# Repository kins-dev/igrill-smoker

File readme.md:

# Starting with Raspberry Pi Stretch 

<!-- markdownlint-disable MD036 -->
**&#x1F534; Note: You are 100% responsible for ensuring safe food practices are followed**

**&#x1F534; Check and modify temperatures as appropriate**
<!-- markdownlint-enable MD036 -->

<!-- markdownlint-disable MD033 -->
<h2>Table of Contents</h2>
<!-- markdownlint-enable MD033 -->
<!-- markdownlint-disable MD039 -->
<!-- @import "[TOC]" {cmd="toc" depthFrom=2 depthTo=6 orderedList=false} -->

<!-- code_chunk_output -->

- [Problem Statement](#problem-statement)
- [Versions](#versions)
- [Design](#design)
- [Equipment](#equipment)
- [Requirements](#requirements)
- [Installation](#installation)
- [Software Setup](#software-setup)
- [Using iGrill Mini](#using-igrill-mini)
- [Grill Setup](#grill-setup)
- [Running](#running)
- [Lighttpd Setup](#lighttpd-setup)
- [Project Notes](#project-notes)
- [iGrill Smoker Board Rev. *A](#igrill-smoker-board-rev-a)
  - [*A Board](#a-board)
  - [*A Notes](#a-notes)
  - [*A Parts](#a-parts)
- [iGrill Smoker Board Rev. *B](#igrill-smoker-board-rev-b)
  - [*B Board](#b-board)
  - [*B Notes](#b-notes)
  - [*B Parts](#b-parts)
- [iGrill Smoker Board Rev. *C](#igrill-smoker-board-rev-c)
  - [*C Board](#c-board)
  - [*C Notes](#c-notes)
  - [*C Parts](#c-parts)
- [iGrill Smoker Board Rev. *D](#igrill-smoker-board-rev-d)
  - [*D Notes](#d-notes)
  - [*D Parts](#d-parts)
- [iGrill Smoker Board Rev. *E](#igrill-smoker-board-rev-e)
  - [*E Notes](#e-notes)
  - [*E Parts](#e-parts)

<!-- /code_chunk_output -->

<!-- markdownlint-enable MD039 -->
## Problem Statement

Create a low cost smoking unit that can be controlled/monitored via the internet.

## Versions

- v1.0: Whole System
- v1.1: BLE Improvements
- v1.2: Python3 Support
- v1.3: Temperature Range Support
- v1.4: SSR Support
- v1.5: PID control

## Design

See the [design document](documentation/iGrill_smoker_design.md).

## Equipment

Prices as of June 10th, 2019.  Some items like the hotplates or skillet can be found at Goodwill instead.  Total cost (new) $287.96.  Every item can be used for more than one task.  Meat, wood chips, and extension cords not included.

- [Weber Grill](https://www.amazon.com/Weber-741001-Original-22-Inch-Charcoal/dp/B00004RALU/ref=sr_1_3) - $109
- [iGrill2](https://www.amazon.com/Weber-7203-iGrill-2-Thermometer/dp/B01MG2CNDL/ref=sr_1_3) - $64.99
- [Hotplate](https://www.amazon.com/Cuisine-ESB-300X-Maxi-Matic-Single-Electric/dp/B0006A2ZTS/ref=sr_1_70) - 2x @ $12.96
- [TP-Link Kasa](https://www.amazon.com/TP-Link-HS100-Required-Google-Assistant/dp/B0178IC734/ref=sr_1_4) - $14.69
- [Raspberry Pi](https://www.target.com/p/raspberry-pi-3-model-b-project-board/-/A-53349740) - $34.49
- [SD Card](https://www.amazon.com/Kingston-Digital-microSDHC-SDC4-8GBSP/dp/B0027CA7UW/ref=sr_1_11) - $3.99
- [Skillets](https://www.amazon.com/dp/B073Q8P6C8/ref=psdc_289821_t1_B00008GKDN) - 2x @ $10.93
- [8 inch rings](https://www.amazon.com/Ateco-14408-8-Inch-Stainless-Cutter/dp/B002A5BU5M/ref=pd_sbs_79_5/140-6446357-6003018) - 2x @ $6.51

## Requirements

You must have:

- Raspberry Pi 3
- TP-Link Kasa
- iGrill2 or iGrill3 (iGrill mini coming soon for time based smoking)

Optional items:

- LEDs with current limiting resistors
- Speaker with 3.5 mm stereo jack input

*Note: This has been tested using a Raspberry Pi B 3 with Raspian Stretch.  Your milage may vary.*

This guide assumes you've done the basic setup of network and updated the system on your Raspberry Pi.  Remember, you probably want to enable ssh access.  You must have your iGrill ready to complete the installation and setup.  This does require python 3 to be installed.

## Installation

Either download and run ```auto-install.sh``` from the installation directory or run the following commands:

```bash
git clone https://git.kins.dev/igrill-smoker
cd igrill-smoker/install
bash run-install.sh
```

After starting the ```run-install.sh``` script, you should turn on your iGrill v2.  Installation shouldn't take long and the device is needed for setup.

## Software Setup

Copy ```config/iGrill_config.example.ini``` to ```config/iGrill_config.ini```.  Update ```iGrill_config.ini``` with any system settings you want to change.

Here is what that file looks like:
<!-- TODO: add > at the end of this line, open MPE, and use shift enter to regenerate --
```bash {cmd hide modify_source}
echo -n \`\`\`ini
cat config/iGrill_config.example.ini
echo -n \`\`\`
```
<!---->

<!-- code_chunk_output -->

```ini
# Copyright (c) 2019:   Scott Atkins <scott@kins.dev>
#                       (https://git.kins.dev/igrill-smoker)
# License:              MIT License
#                       See the LICENSE file
[iGrill]
# can be Standard or Mini
Type=Standard

[Probes]
# For iGrill mini set food probe to 0 and smoke probe to 1

# Food probe must be set between 0 and 4, where 0 means the
# probe is disabled.  The left most probe is 1 and right most
# is 4 on the iGrill 2/3
#
# If you disable the food probe, you must use a stage that
# is iGrill mini compatible (see stage file) or disable stages
FoodProbe=1

# Smoke probe must be set between 1 and 4.  The left most probe
# is 1 and right most is 4 on the iGrill 2/3
SmokeProbe=4

[RuntimeFiles]
# Where the limits file should exist, relative to the project
# directory
LimitsFile=limits.ini
TempDataFile=igrill.json

[Logging]
LogLevel=INFO
LogFile=

[Kasa]
# Name of your plug in the Kasa app, case sensitive
Name=iGrill-smoker

[Smoking]
MaxTempChange=2
TempBandSize=7

# Can be the name of any file in the stages directory (excluding the .sh) or None
Food=brisket

# Only valid if Food=None
SmokeMid=225
InternalTarget=185

# Used to specify the solid state relay board
[SSR]
# Possible values:
#  **, *A, *B, *C, *D, *D.1, *E, Auto, None
Board=Auto

[Reporting]
# time in seconds between polls of the iGrill
# faster polling means more power use
PollTime=20

ResultsDirectory=/var/www/html
CSVFile=current.csv
StateFile=state.json
```

<!-- /code_chunk_output -->

Edit the chart.html file in the website_example directory to suit your needs and copy it to your ```/var/www/html``` directory.

## Using iGrill Mini

The iGrill mini has a single probe.  That means you can either monitor the smoke temperature or the food temperature.  Since this is controlling a plug for the smoke, you should not monitor the food temperature via the iGrill mini probe.  Follow the instructions in iGrill_config.example.ini for setting the probe values.

## Grill Setup

## Running

Start a smoking session by running:

```bash
./start_smoking.sh
```

## Lighttpd Setup

Secure your instance of lighttpd using the instructions at <https://github.com/galeone/letsencrypt-lighttpd/blob/master/renew.sh>.  You may want a wildcard certificate and you can find instructions via <https://asknetsec.com/generate-lets-encrypt-free-wildcard-certificate-using-certbot-ubuntu-16-04/>.  Check your SSL setup via <https://www.ssllabs.com/ssltest/index.html>.

Also, it may be a good idea to setup lighttpd such that ```*.csv```/```*.json``` is not cached.  Here's an example lighttpd config file:

```ruby
server.modules = (
        "mod_expire",
        "mod_access",
        "mod_alias",
        "mod_compress",
        "mod_redirect",
        "mod_setenv",
        "mod_dirlisting",
)

server.document-root                            = "/var/www/html"
server.upload-dirs                              = ( "/var/cache/lighttpd/uploads" )
server.errorlog                                 = "/var/log/lighttpd/error.log"
server.pid-file                                 = "/var/run/lighttpd.pid"
server.username                                 = "www-data"
server.groupname                                = "www-data"
server.port                                     = 80

index-file.names                                = ( "index.php", "index.html", "index.lighttpd.html" )
url.access-deny                                 = ( "~", ".inc" )
static-file.exclude-extensions                  = ( ".php", ".pl", ".fcgi" )

compress.cache-dir                              = "/var/cache/lighttpd/compress/"
compress.filetype                               = ( "application/javascript", "text/css", "text/html", "text/plain" )

# default listening port for IPv6 falls back to the IPv4 port
## Use ipv6 if available
#include_shell "/usr/share/lighttpd/use-ipv6.pl " + server.port
include_shell "/usr/share/lighttpd/create-mime.assign.pl"
include_shell "/usr/share/lighttpd/include-conf-enabled.pl"

# SSL Config
$SERVER["socket"] == ":443" {
        protocol                                = "https://"
        ssl.engine                              = "enable"
        ssl.ca-file                             = "/etc/lighttpd/fullchain.pem"
        ssl.pemfile                             = "/etc/lighttpd/wildcard.cert.pem"

        setenv.add-environment  = (
                "HTTPS"                         => "on"
        )

        setenv.add-response-header  = (
                # Allow cross domain access
                # Safari requires *
                "Access-Control-Allow-Origin"   => "*",

                # Used to identify the server based on headers
                "Server"                        => "Server name",

                # Set timeout for ssl access
                "Strict-Transport-Security"     => "max-age=15768000;"
        )

        # Mitigate BEAST attack:
        #
        # A stricter base cipher suite. For details see:
        # http://blog.ivanristic.com/2011/10/mitigating-the-beast-attack-on-tls.html
        ssl.cipher-list                         = "ECDHE-ECDSA-AES256-GCM-SHA384:ECDHE-RSA-AES256-GCM-SHA384:ECDHE-ECDSA-CHACHA20-POLY1305:ECDHE-RSA-CHACHA20-POLY1305:ECDHE-ECDSA-AES128-GCM-SHA256:ECDHE-RSA-AES128-GCM-SHA256:ECDHE-ECDSA-AES256-SHA384:ECDHE-RSA-AES256-SHA384:ECDHE-ECDSA-AES128-SHA256:ECDHE-RSA-AES128-SHA256"

        # Make the server prefer the order of the server side cipher suite instead of the client suite.
        # This is necessary to mitigate the BEAST attack (unless you disable all non RC4 algorithms).
        # This option is enabled by default, but only used if ssl.cipher-list is set.
        ssl.honor-cipher-order                  = "enable"

        # Mitigate CVE-2009-3555 by disabling client triggered renegotiation
        # This is enabled by default.
        ssl.disable-client-renegotiation        = "enable"
        ssl.ec-curve                            = "secp384r1"
        ssl.use-compression                     = "disable"

        # Disable SSLv2 because is insecure
        ssl.use-sslv2                           = "disable"

        # Disable SSLv3 (can break compatibility with some old browser) /cares
        ssl.use-sslv3                           = "disable"
}

# Prevent caching of json/csv files
$HTTP["url"] =~ "/.*\.(json|csv)$" {
        expire.url = (
                ""                              => "access 0 seconds",
        )
}
```

## Project Notes

1.3 Uses TP-Link Kasa for power control.  1.4 includes a brand new power control board that plugs into the Raspberry Pi which will allow much more fine grain control of the smoker temperature.

This is necessary because the relay in the TP-Link won't handle the number of on/off cycles required.  Instead a solid state relay is used.  A word of caution, this is not UL rated or certified.  If you don't know which end of the soldering iron to hold, then you probably should just stick with 1.3.

The TP-Link Kasa plug will still be used as a failsafe device in the system.

## iGrill Smoker Board Rev. *A

### *A Board

This board has a buzzer, two LEDs and connection points for the solid state relay.  It sits off the edge of the Raspberry Pi GPIOs.

### *A Notes

This board should not be used.

Features

- Two LEDs
- Buzzer
- Small design

Defects

- The spacing for the resistors is off
- Hard to hand solder
- Hangs off the board the wrong way
- Red LED stays on due to leakage current
- Leakage current to the SSR

### *A Parts

- Header (2x20): [DigiKey](https://www.digikey.com/product-detail/en/sullins-connector-solutions/SFH11-PBPC-D20-ST-BK/S9200-ND/1990093) $1.94
- LED (Green): [DigiKey](https://www.digikey.com/product-detail/en/lite-on-inc/LTL-4233/160-1130-ND/217580) $0.36
- LED (Red): [DigiKey](https://www.digikey.com/product-detail/en/wurth-electronics-inc/151051RS11000/732-5016-ND/4490012) $0.15
- Resistors (100 ohm x2): [DigiKey](https://www.digikey.com/product-detail/en/stackpole-electronics-inc/CF14JT100R/CF14JT100RCT-ND/1830327) $0.10
- Buzzer: [DigiKey](https://www.digikey.com/product-detail/en/tdk-corporation/PS1240P02BT/445-2525-1-ND/935930) $0.68

## iGrill Smoker Board Rev. *B

### *B Board

This board has a buzzer, two LEDs and connection points for the solid state relay.  It sits on the Raspberry Pi GPIOs.

### *B Notes

This board should not be used.

New Features

- Sits over the Pi with mounting holes
- Board auto detect works
- Buzzer switch

Defects

- The spacing for the resistors is off
- The QR code doesn't always read correctly
- The solder mask makes it hard to read the @ symbol
- Red LED stays on due to leakage current
- Buzzer makes a sound when it shouldn't
- Leakage current to the SSR

### *B Parts

- Header (2x20): [DigiKey](https://www.digikey.com/product-detail/en/sullins-connector-solutions/SFH11-PBPC-D20-ST-BK/S9200-ND/1990093) $1.94
- LED (Green): [DigiKey](https://www.digikey.com/product-detail/en/lite-on-inc/LTL-4233/160-1130-ND/217580) $0.36
- LED (Red): [DigiKey](https://www.digikey.com/product-detail/en/wurth-electronics-inc/151051RS11000/732-5016-ND/4490012) $0.15
- Resistors (100 ohm x2): [DigiKey](https://www.digikey.com/product-detail/en/stackpole-electronics-inc/CF14JT100R/CF14JT100RCT-ND/1830327) $0.10
- Buzzer: [DigiKey](https://www.digikey.com/product-detail/en/tdk-corporation/PS1240P02BT/445-2525-1-ND/935930) $0.68
- Switch: [DigiKey](https://www.digikey.com/product-detail/en/c-k-components/JS202011CQN/401-2001-ND/1640097) $0.43

## iGrill Smoker Board Rev. *C

### *C Board

This board has a buzzer, two LEDs and a terminal block for the solid state relay.  It sits on the Raspberry Pi GPIOs.

### *C Notes

This board is currently in production and has not been tested.

New Features

- NPN transistors to remove leakage

Fixes

- QR Code
- Resistor spacing
- Solder mask changed to silk screen for fine pitch
- Using suggested design for the buzzer

Defects

- Leakage current to the SSR
- Missing resistors on NPN transistor base (good design practice)

### *C Parts

- Header (2x20): [DigiKey](https://www.digikey.com/product-detail/en/sullins-connector-solutions/SFH11-PBPC-D20-ST-BK/S9200-ND/1990093) $1.94
- LED (Green): [DigiKey](https://www.digikey.com/product-detail/en/lite-on-inc/LTL-4233/160-1130-ND/217580) $0.36
- LED (Red): [DigiKey](https://www.digikey.com/product-detail/en/wurth-electronics-inc/151051RS11000/732-5016-ND/4490012) $0.15
- Resistors (100 ohm x3): [DigiKey](https://www.digikey.com/product-detail/en/stackpole-electronics-inc/CF14JT100R/CF14JT100RCT-ND/1830327) $0.10
- Buzzer: [DigiKey](https://www.digikey.com/product-detail/en/tdk-corporation/PS1240P02BT/445-2525-1-ND/935930) $0.68
- Switch: [DigiKey](https://www.digikey.com/product-detail/en/c-k-components/JS202011CQN/401-2001-ND/1640097) $0.43
- Transistors (NPN x3): [DigiKey](https://www.digikey.com/product-detail/en/micro-commercial-co/2N3904-AP/2N3904-APCT-ND/950591) $0.19

## iGrill Smoker Board Rev. *D

This board has a buzzer, seven LEDs and connection points for the solid state relay.  It sits on the Raspberry Pi GPIOs.

### *D Notes

The boards back from production are bad

New Features

- Five new LEDs for temperature monitoring
- Surface mount parts
- Mosfet transistors so a resistor is no longer needed
- Transistor to prevent SSR leakage
- Cheaper parts

Defects

- Silk screen issue
- QR Code issue (too small, inverted on back)
- Transistors wired backwards

### *D Parts

TODO: Add part list

## iGrill Smoker Board Rev. *E

This board has a buzzer, seven LEDs and connection points for the solid state relay.  It sits on the Raspberry Pi GPIOs.  It also has jumpers for a board id number

### *E Notes

This board is not yet in production and has not been tested.

New Features

- New QR code
- Pull down resistors for all transistors

Defects

- None found yet

### *E Parts

TODO: Add part list

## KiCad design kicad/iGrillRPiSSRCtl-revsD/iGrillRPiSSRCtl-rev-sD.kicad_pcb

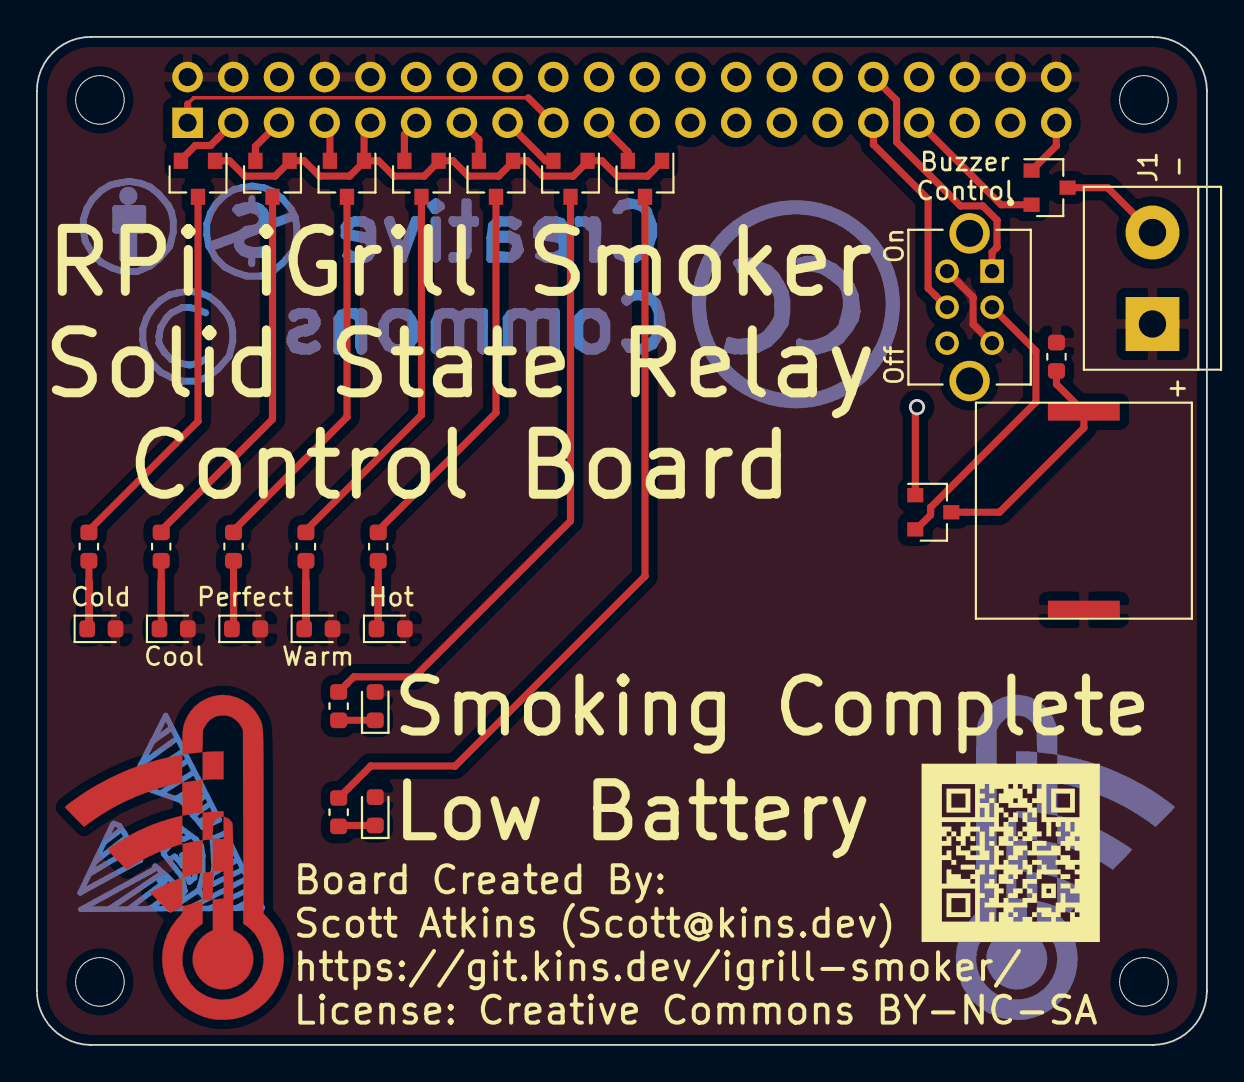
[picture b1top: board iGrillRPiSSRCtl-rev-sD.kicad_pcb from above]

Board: 2 copper layers, 65.0 x 56.0 mm, 32 parts (1 on the bottom side), 30 nets.

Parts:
BZ1: Buzzer; Buzzer_KELIKING_KLJ-1230-smd
D1: Low Battery; LED_0603_1608Metric
D2: Smoking Complete; LED_0603_1608Metric
D3: Hot; LED_0603_1608Metric
D4: Warm; LED_0603_1608Metric
D5: Perfect; LED_0603_1608Metric
D6: Cool; LED_0603_1608Metric
D7: Cold; LED_0603_1608Metric
J1: Screw_Terminal_01x02; TerminalBlock_bornier-2_P5.08mm
MK1, MK2, MK3, MK4: M2.5; MountingHole_2.7mm_M2.5
P1: Conn_02x20_Odd_Even; PinSocket_2x20_P2.54mm_Vertical
Q1, Q2, Q3, Q4, Q5, Q6, Q7, Q8, Q9: Q_NPN_ECB; SOT-23
R1, R5, R6, R8, R9: 120Ω; R_0603_1608Metric
R2, R7: 82Ω; R_0603_1608Metric
R4: 1kΩ; R_0603_1608Metric
SW1: Off On; SW_OS202011MS2QS1

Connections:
+3V3: P1.1, P1.17
+5V: BZ1.1, D1.2, D2.2, D3.2, D4.2, D5.2, D6.2, D7.2, J1.1, P1.2, P1.4, P1.8, P1.10, P1.36, P1.38, P1.40, R4.1, SW1.3, SW1.4
/GPIO2(SDA1): P1.3, Q8.2
/GPIO3(SCL1): P1.5, Q7.2
/GPIO4(GCLK): P1.7, Q6.2
/GPIO6: P1.31, SW1.5
/GPIO10(SPI0_MOSI): P1.19, Q2.2
/GPIO12(PWM0): P1.32, SW1.1
/GPIO13(PWM1): P1.33, Q9.2
/GPIO17(GEN0): P1.11, Q5.2
/GPIO22(GEN3): P1.15, Q3.2
/GPIO27(GEN2): P1.13, Q4.2
GND: P1.6, P1.9, P1.12, P1.14, P1.16, P1.18, P1.20, P1.22, P1.24, P1.25, P1.26, P1.30, P1.34, P1.39, Q1.1, Q2.1, Q3.1, Q4.1, Q5.1, Q6.1, Q7.1, Q8.1, Q9.1, SW1.6
unnamed: BZ1.2, Q1.3, R4.2
unnamed: D1.1, R1.1
unnamed: D2.1, R2.1
unnamed: D3.1, R5.1
unnamed: D4.1, R6.1
unnamed: D5.1, R7.1
unnamed: D6.1, R8.1
unnamed: D7.1, R9.1
unnamed: J1.2, Q9.3
unnamed: Q1.2, SW1.2
unnamed: Q2.3, R1.2
unnamed: Q3.3, R2.2
unnamed: Q4.3, R5.2
unnamed: Q5.3, R6.2
unnamed: Q6.3, R7.2
unnamed: Q7.3, R8.2
unnamed: Q8.3, R9.2

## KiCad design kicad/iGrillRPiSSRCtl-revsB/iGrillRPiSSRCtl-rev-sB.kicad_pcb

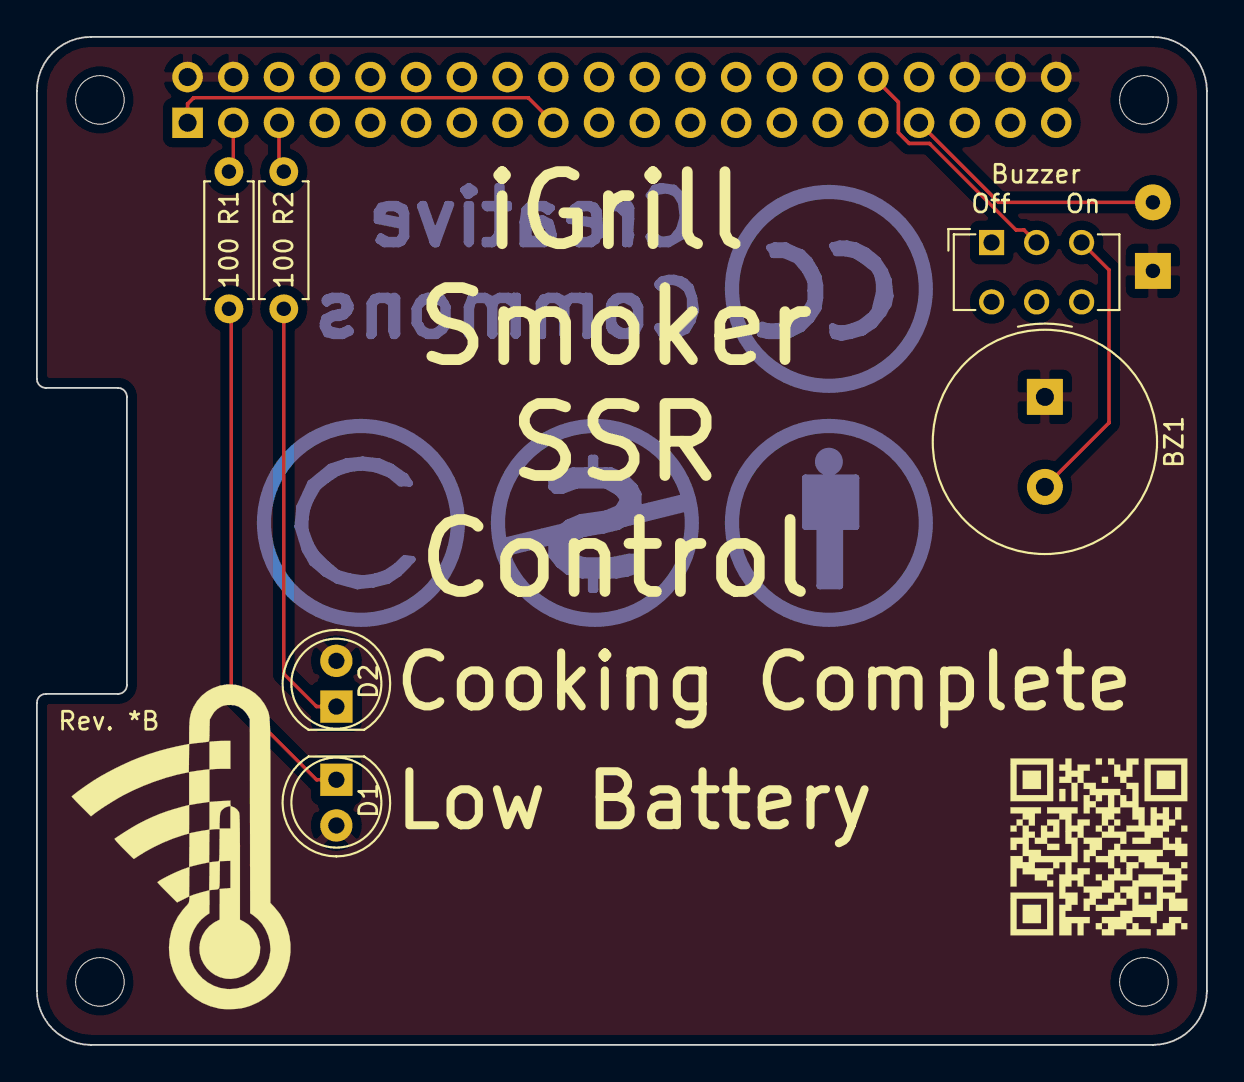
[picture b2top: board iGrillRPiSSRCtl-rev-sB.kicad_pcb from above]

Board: 2 copper layers, 65.0 x 56.0 mm, 12 parts (1 on the bottom side), 10 nets.

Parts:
BZ1: Buzzer; Buzzer_TDK_PS1240P02BT_D12.2mm_H6.5mm
D1: Low Battery; LED_D5.0mm
D2: Cooking Complete; LED_D5.0mm_Clear
J1: Conn_01x02; SolderWirePad_1x02_P3.81mm_Drill0.8mm
MK1, MK2, MK3, MK4: M2.5; MountingHole_2.7mm_M2.5
Off    On: SW_DPDT_x2; SW_CuK_JS202011CQN_DPDT_Straight
P1: Conn_02x20_Odd_Even; PinSocket_2x20_P2.54mm_Vertical
R1, R2: 100; R_Axial_DIN0207_L6.3mm_D2.5mm_P7.62mm_Horizontal

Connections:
+3V3: P1.1, P1.17
+5V: BZ1.1, D1.2, D2.2, J1.1, P1.2, P1.4, P1.8, P1.36, P1.38, P1.40
/GPIO2(SDA1): P1.3, R1.1
/GPIO3(SCL1): P1.5, R2.1
/GPIO12(PWM0): Off On.2, P1.32
/GPIO13(PWM1): J1.2, P1.33
GND: P1.6, P1.9, P1.10, P1.12, P1.14, P1.16, P1.18, P1.20, P1.22, P1.24, P1.25, P1.26, P1.30, P1.34, P1.39
unnamed: BZ1.2, Off On.3
unnamed: D1.1, R1.2
unnamed: D2.1, R2.2

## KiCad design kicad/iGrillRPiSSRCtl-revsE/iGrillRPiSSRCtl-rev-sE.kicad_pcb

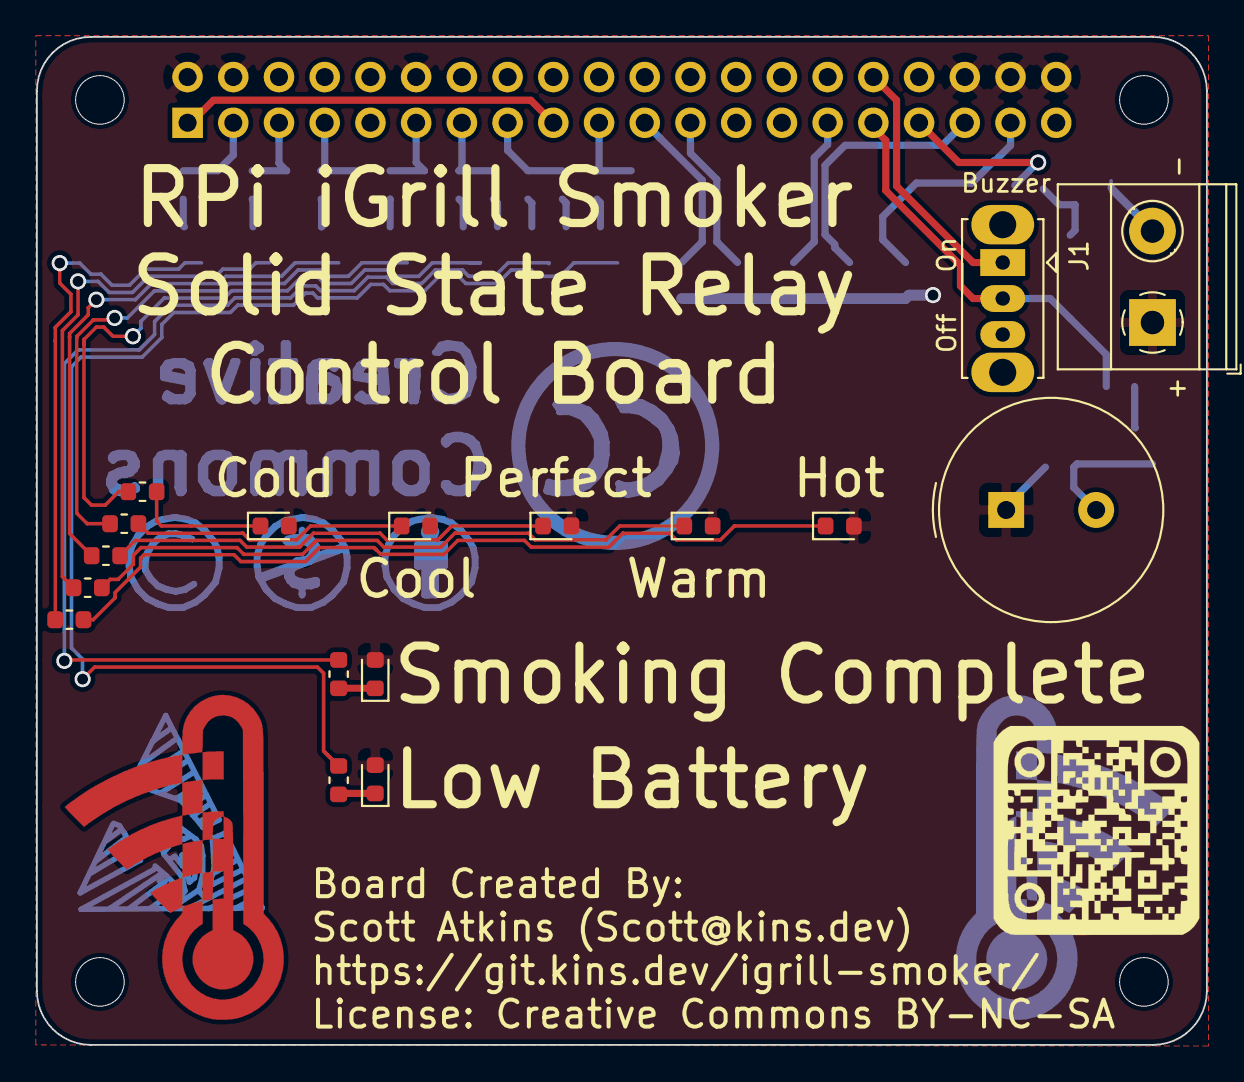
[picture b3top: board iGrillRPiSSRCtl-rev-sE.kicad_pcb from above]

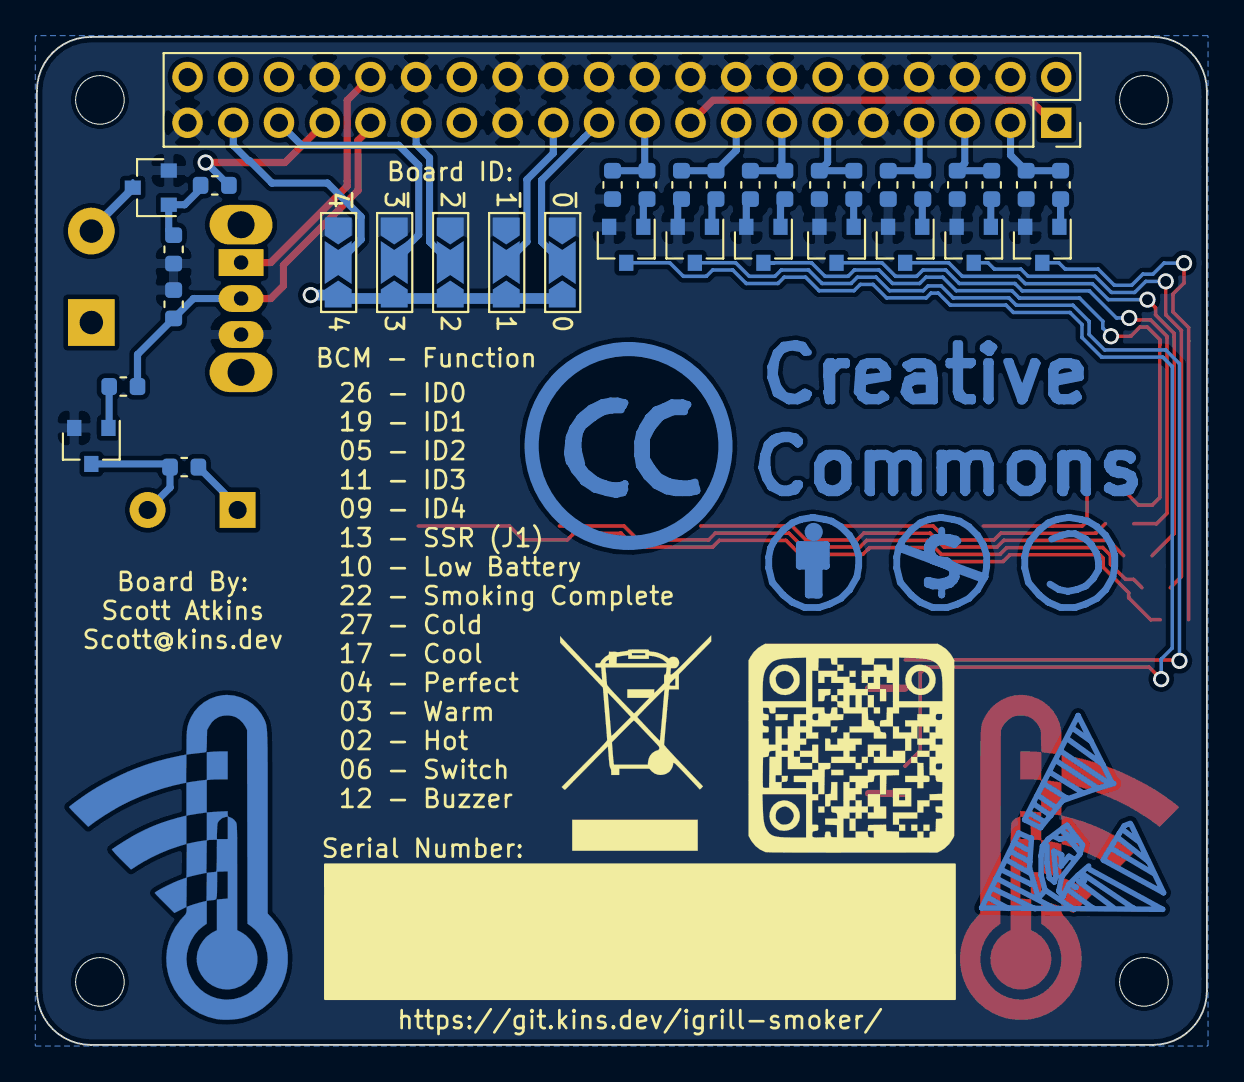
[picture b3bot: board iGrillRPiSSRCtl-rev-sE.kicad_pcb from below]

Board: 2 copper layers, 65.0 x 56.0 mm, 55 parts (34 on the bottom side), 43 nets.

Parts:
BZ1: Buzzer; Buzzer_TDK_PS1240P02BT_D12.2mm_H6.5mm
D1: Low Battery; LED_0603_1608Metric
D2: Smoking Complete; LED_0603_1608Metric
D3: Cold; LED_0603_1608Metric
D4: Cool; LED_0603_1608Metric
D5: Perfect; LED_0603_1608Metric
D6: Warm; LED_0603_1608Metric
D7: Hot; LED_0603_1608Metric
J1: Screw_Terminal_01x02; TerminalBlock_Phoenix_MKDS-1,5-2-5.08_1x02_P5.08mm_Horizont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
JP1, JP2, JP3, JP4, JP5: Jumper_3_Open; SolderJumper-3_P2.0mm_Open_TrianglePad1.0x1.5mm_NumberLabels
MK1, MK2, MK3, MK4: M2.5; MountingHole_2.7mm_M2.5
P1: Conn_02x20_Odd_Even; PinSocket_2x20_P2.54mm_Vertical
Q1, Q2, Q3, Q4, Q5, Q6, Q7, Q8, Q9: MMBT3904LT1G; SOT-23
R1, R3, R5, R7, R9, R12, R14: 180Ω; R_0603_1608Metric
R2, R4, R6, R8, R10, R11, R13, R15, R16, R17: 1kΩ; R_0603_1608Metric
R18, R19, R20, R21, R22, R23, R24, R25, R26: 10kΩ; R_0603_1608Metric
SW1: SW_SPDT; SW_Slide_1P2T_CK_OS102011MS2Q

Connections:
+3V3: P1.1, P1.17
+5V: BZ1.1, D1.2, D2.2, D3.2, D4.2, D5.2, D6.2, D7.2, J1.1, JP1.3, JP2.3, JP3.3, JP4.3, JP5.3, P1.2, P1.4, P1.12, P1.36, P1.38, P1.40, R17.1
/GPIO2(SDA1): P1.3, R15.2, R25.1
/GPIO3(SCL1): P1.5, R13.2, R24.1
/GPIO4(GCLK): P1.7, R10.2, R23.1
/GPIO5: JP3.2, P1.29
/GPIO6: P1.31, R16.1, R26.2, SW1.2
/GPIO9(SPI0_MISO): JP1.2, P1.21
/GPIO10(SPI0_MOSI): P1.19, R2.2, R18.1
/GPIO11(SPI0_SCK): JP2.2, P1.23
/GPIO12(PWM0): P1.32, SW1.1
/GPIO13(PWM1): P1.33, R11.1
/GPIO17(GEN0): P1.11, R8.2, R21.1
/GPIO19(SPI1_MISO): JP4.2, P1.35
/GPIO22(GEN3): P1.15, R4.2, R19.1
/GPIO26: JP5.2, P1.37
/GPIO27(GEN2): P1.13, R6.2, R20.1
GND: JP1.1, JP2.1, JP3.1, JP4.1, JP5.1, P1.6, P1.8, P1.9, P1.10, P1.14, P1.16, P1.18, P1.20, P1.22, P1.24, P1.25, P1.26, P1.30, P1.34, P1.39, Q1.2, Q2.2, Q3.2, Q4.2, Q5.2, Q6.2, Q7.2, Q8.2, Q9.2, R18.2, R19.2, R20.2, R21.2, R22.1, R23.2, R24.2, R25.2, R26.1, SW1.3
unnamed: BZ1.2, Q9.3, R17.2
unnamed: D1.1, R1.1
unnamed: D2.1, R3.1
unnamed: D3.1, R5.1
unnamed: D4.1, R7.1
unnamed: D5.1, R9.1
unnamed: D6.1, R12.1
unnamed: D7.1, R14.1
unnamed: J1.2, Q6.3
unnamed: Q1.1, R2.1
unnamed: Q1.3, R1.2
unnamed: Q2.1, R4.1
unnamed: Q2.3, R3.2
unnamed: Q3.1, R6.1
unnamed: Q3.3, R5.2
unnamed: Q4.1, R8.1
unnamed: Q4.3, R7.2
unnamed: Q5.1, R10.1
unnamed: Q5.3, R9.2
unnamed: Q6.1, R11.2, R22.2
unnamed: Q7.1, R13.1
unnamed: Q7.3, R12.2
unnamed: Q8.1, R15.1
unnamed: Q8.3, R14.2
unnamed: Q9.1, R16.2

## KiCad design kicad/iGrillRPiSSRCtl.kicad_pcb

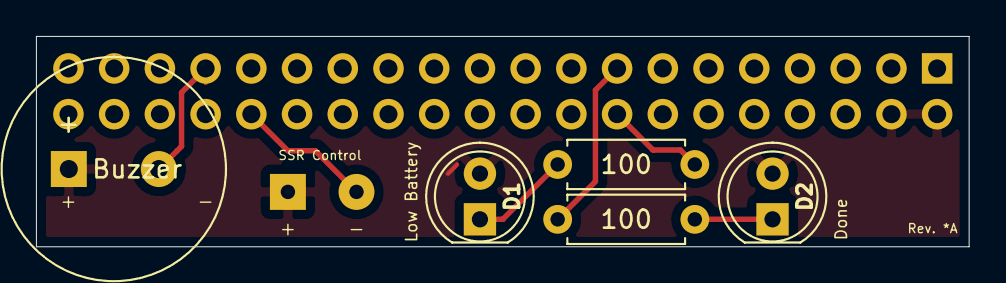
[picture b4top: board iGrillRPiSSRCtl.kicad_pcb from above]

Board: 2 copper layers, 51.8 x 11.7 mm, 7 parts (1 on the bottom side), 7 nets.

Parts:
BZ1: Buzzer; Buzzer_TDK_PS1240P02BT_D12.2mm_H6.5mm
D1: Low Battery; LED_D5.0mm
D2: Done; LED_D5.0mm_Clear
J1: Raspberry_Pi_2_3; PinSocket_2x20_P2.54mm_Vertical
J2: SSR Control; SolderWirePad_1x02_P3.81mm_Drill0.8mm
R1, R2: 100; R_Axial_DIN0207_L6.3mm_D2.5mm_P7.62mm_Horizontal

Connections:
+5V: BZ1.1, D1.2, D2.2, J1.2, J1.4, J2.1
unnamed: BZ1.2, J1.33
unnamed: D1.1, R1.2
unnamed: D2.1, R2.2
unnamed: J1.15, R2.1
unnamed: J1.16, R1.1
unnamed: J1.32, J2.2

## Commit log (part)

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2019-04-09 SSL test site
2019-04-09 Grammar cleanup
2019-04-10 Remove confusing class
2019-04-10 Removing pycrypt
2019-04-11 syntax error fix
2019-04-11 Updating to relative path
2019-04-11 Adding stage time to the state file
2019-04-12 Formatting Cleanup
2019-04-12 Cleanup based on shellcheck
2019-04-12 Code cleanup
2019-04-13 quoting in if statements
2019-04-13 Updating set line
2019-04-13 shellcheck changes
2019-04-13 Making get_mac work with iGrill3
2019-04-13 Making things consistent
2019-04-13 Fixes for subshell
2019-04-13 Cleanup of the reset
2019-04-14 Documentation Changes
2019-04-14 Fix for line endings
2019-04-14 updates to documentation
2019-04-19 Adding documenation
2019-04-19 coproc update to fix shellcheck warning
2019-04-22 Changes from testing
2019-04-24 Remove pycrypt again
2019-04-24 Adding documentation
2019-04-24 Ignoring settings file for vscode
2019-04-24 Updating logging
2019-04-25 changing logging
2019-04-25 Fixing syntax
2019-04-25 cleanup for LE and thresholds
2019-04-25 Fixing ignored data value
2019-04-26 Fixing bad syntax
2019-04-26 more syntax fixes
2019-04-26 Changes based on testing
2019-04-26 fix from pylint
2019-04-26 Cleaning up code
2019-04-27 Updating bad data value based on test
2019-04-27 Moving to python3
2019-04-27 updates for python3
2019-04-27 Syntax fix
2019-04-27 Small structure changes
2019-04-27 Updating documentation
2019-04-28 Doc updat
2019-04-29 Starting iGrill mini code
2019-04-29 Updating style
2019-04-30 allow user to specify igrill mini
2019-04-30 Fixed syntax error
2019-04-30 Style cleanup
2019-05-01 Updates for shellcheck
2019-05-02 Cleanup
2019-05-05 System restructuring
2019-05-05 Moving files around
2019-05-05 Fixing markdown
2019-05-05 Moving to absolute paths
2019-05-05 Moving to mostly absolute paths
2019-05-05 Updating install instructions
2019-05-05 Updating script names and documenation
2019-05-05 Documentation updates
2019-05-05 Moving files back to fix github warnings
2019-05-05 fixing directory
2019-05-06 Permission fixes
2019-05-06 Adding first pull request template
2019-05-06 Update of template
2019-05-06 Fixing filename
2019-05-06 Changes to allow stages to adjust controls
2019-05-06 Trying to get pull request template to work
2019-05-06 Changing names
2019-05-06 Moving folder
2019-05-06 Yet another move
2019-05-06 Hiding file
2019-05-06 Adding PR template
2019-05-06 Fixing path to python files
2019-05-07 Script fixes
2019-05-07 Attempting to fix 1.2
2019-05-08 Revert of char handling
2019-05-08 Moving around python scripts
2019-05-08 Adding single shot test mode
2019-05-08 Going back to null string
2019-05-08 Fixing issues with disconnects
2019-05-08 Space cleanup
2019-05-09 Adding iGrillChars
2019-05-09 Updating threshold parsing
2019-05-09 Building ini defaults
2019-05-09 Adding INI config settings
2019-05-10 fix for array indexing
2019-05-10 Updating data order
2019-05-10 refactoring
2019-05-10 Split out kasa functions
2019-05-11 Spelling fixes, documentation fixes
2019-05-11 Moving comments
2019-05-11 moving config around
2019-05-12 More setup for mini support
2019-05-12 Rewriting for ini file
2019-05-12 parser cleanup and test
2019-05-12 More ini changes
2019-05-12 Move over to ini completely, suport for mini
2019-05-12 fix for copy paste error
2019-05-13 Updating copyright notices
2019-05-19 structure and documentation changes
2019-05-20 Ini cleanup
2019-05-20 Documentation update + error handling
2019-05-20 Adding todo reminder
2019-05-20 Updated error handling
2019-05-20 Fixing lint items
2019-05-20 Spelling fixes
2019-05-20 Adding design documentation
2019-05-20 Adding copyright
2019-05-21 Documentation Cleanup
2019-05-21 todos + fix for probe
2019-05-22 Script cleanup
2019-05-22 Documenation updates
2019-05-23 Getting Kasa IP automatically
2019-05-23 Documentation update
2019-05-23 Removing Kasa search
2019-05-23 Faster processing and test
2019-05-24 fixing path
2019-05-24 check arg count
2019-05-25 Code for setting limits
2019-05-25 Moving limits to own file
2019-05-26 Limits in place Name cleanup
2019-05-27 Adding link
2019-05-27 Adding files section
2019-05-27 Adding more file data
2019-05-27 Removing unneeded files
2019-05-27 File cleanup
2019-05-27 Adding key
2019-05-28 bash script documentation
2019-05-28 Filling out bash file list
2019-05-29 more file info
2019-05-29 Moving topics around
2019-05-30 Finishing documentation
2019-06-01 Start of shrink limits
2019-06-02 Changed diff to be absolute
2019-06-10 Documentation and LED clearing
2019-06-10 Adding extra item
2019-06-12 Kasa python intial build
2019-06-12 Finishing script
2019-06-12 Removed npm and the kasa cli
2019-06-12 rebuilding to use new python script
2019-06-13 Change file name to avoid collision Started on daemon
2019-06-13 adding socket
2019-06-13 move to pyro5
2019-06-13 Retry discovery
2019-06-13 Adding on and off commands
2019-06-14 Better performance
2019-06-14 Documentation
2019-06-15 Moving print messages to logging
2019-06-15 client has option processing
2019-06-15 moving to kasa daemon
2019-06-15 Making longer smoking session
2019-06-16 Removing unneeded file
2019-06-19 Threading prototype
2019-06-22 Comments
2019-06-23 Doc updates
2019-06-25 Adding KiCad Files
2019-06-25 Rev *A changes
2019-06-25 Finishing *A layout
2019-06-26 Added to readme
2019-06-26 Doc cleanup
2019-06-26 License update
2019-06-26 Board update for parts
2019-06-26 *B Board Rev
2019-06-27 File rename
2019-06-27 File naming consistency *C Board
2019-06-27 Board cleanup
2019-06-27 Electrical Cleanup of Schematic
2019-07-03 Board updates
2019-07-03 footprint update
2019-07-03 Fixing pinout for RPi PWMs
2019-07-03 Updated design to fix issues from protoype
2019-07-04 Updates from protoype **
2019-07-05 Building SSR control
2019-07-06 Adding led control code
2019-07-06 LEDs should work now
2019-07-06 updated pins
2019-07-07 Detecting board type
2019-07-07 Board detection
2019-07-07 Adding board detect
2019-07-07 Adding SSR control
2019-07-08 Syntax fixes
2019-07-08 Updating board design
2019-07-08 Adding *D
2019-07-08 Moving to smd devices
2019-07-09 Adding *B ID
2019-07-09 Cleanup and fixes
2019-07-09 Fixing bad merge
2019-07-09 Attempting to get my board made
2019-07-10 Updated schematic, pcb for board id
2019-07-10 *D changes
2019-07-10 *D Complete and sent off
2019-07-11 Started to add *D board to the scripts
2019-07-11 Updated docs
2019-07-12 Adding *D board support
2019-07-12 Documenting board types
2019-07-12 Updating notes
2019-07-14 Readme Updates
2019-07-16 adding footprints
2019-07-19 Adding *E
2019-07-20 Updated constants
2019-07-20 starting buzzer
2019-07-20 data structure rewrite
2019-07-21 Buzzer updates
2019-07-21 Buzzer changes
2019-07-21 Syntax changes
2019-07-21 Fixing exit command
2019-07-22 Trying new import syntax
2019-07-23 Header changes + unittests
2019-07-23 Unittest up and running
2019-07-23 test updates
2019-07-23 restructure to run properly
2019-07-24 python restructuring
2019-07-24 fixing paths
2019-07-25 Finish conversion to new structure
2019-07-25 Fixing copy/paste error
2019-07-25 Moved to python board control
2019-07-26 Trying to add unittests
2019-07-27 Board Unittests Working
2019-07-27 Add leds unittest
2019-07-27 Moving kasa test to mock objects
2019-07-27 Fixing travis ci run command
2019-07-27 Swapped top and start
2019-07-27 Updating requirements
2019-07-27 Adding buzzer test stub
2019-07-28 Adding board checkout script
2019-07-28 Full LED checkout
2019-07-28 adding buzzer tests
2019-07-28 Adding delay for daemon startup
2019-07-28 Shellcheck/spelling cleanup
2019-07-28 Build status on Readme
2019-07-28 Fixing buzzer
2019-07-28 Fixing division
2019-07-28 SSR Daemon bones in place
2019-07-29 Adding buzzer test
2019-07-29 Adding todo
2019-07-30 Cleanup of constants
2019-07-30 Fixing test, constant cleanup
2019-07-30 Better Kasa testing
2019-07-30 Fixed unittest
2019-07-31 Updating buzzer and design for *e
2019-08-01 Adding patched board
2019-08-01 Updated config reading
2019-08-01 *E board updates
2019-08-03 *E updates
2019-08-03 Fixing pulldown resistors
2019-08-03 *E documentation
2019-08-04 Adding SSR and better thread handling
2019-08-04 Magic number cleanup + SSR
2019-08-05 Adding script to process gerber files
2019-08-05 Fixed References
2019-08-07 *E updates before production
2019-08-07 Image update
2019-08-08 Moving to SSR Control - Needs testing
2019-08-09 Fix for relay pin
2019-08-09 removing unneeded function
2019-08-09 fixing names
2019-08-09 fixing mac address check
2019-08-09 fixing import
2019-08-09 Fixing startup/shutdown
2019-08-09 fixed sys path issues
2019-08-09 fix for status
2019-08-09 Fix for relay
2019-08-09 Trying to fix ctl-c
2019-08-09 Fix for ssrc exit
2019-08-10 Cleanup and Documentation
2019-08-10 Cleanup of kasa
2019-08-10 Adding debug messages
2019-08-10 Path clean, adjust in band handling
2019-08-10 fixing invalid arg
2019-08-10 removing some debug outpu
2019-08-10 Adding more debug
2019-08-10 Adding more debugging
2019-08-10 Debugging why max change is incorrect
2019-08-10 fix for max temp change
2019-08-10 Changing up/down speed
2019-08-10 Updated text
2019-08-10 Updated inband behavior
2019-08-10 adding limits to all on/off
2019-08-10 Updating sttart value
2019-08-10 Fix for minimum SSRC value
2019-08-10 Adding daemon log files
2019-08-10 debug print statements
2019-08-10 Disabling debug print statements
2019-08-11 Changing limits based on testing
2019-08-12 Changing initial SSR value
2019-08-14 Added tasks, updated tests, added *E
2019-08-15 Added board checkout task, updated host names
2019-08-16 More documentation updates
2019-08-16 Fixing display issue in GitHub
2019-08-17 Added how to make a stage
2019-08-18 Updated schedules/comments/docs
2019-08-18 adding screen config
2019-08-18 Default windows
2019-08-18 setting up intial screens
2019-08-18 Update to vscode tasks
2019-08-18 Added start smoking task
2019-08-19 Updated schedule
2019-08-19 Updated pull request template
2019-08-19 Update of schedule for current run
2019-08-20 Way to get status
2019-08-21 Updated to prevent failures
2019-08-21 Set all variables before they can be used
2019-08-21 More error logging
2019-08-21 Better error message
2019-08-21 Adaptive timeout
2019-08-21 Attempting to fix discover
2019-08-21 Fixing detection
2019-08-21 Adding debug
2019-08-21 More debug
2019-08-21 Fixing return
2019-08-21 More discovery changes
2019-08-21 Adding SSR % to CSV file
2019-08-22 Rewrite of Kasa daemon to prevent network errors
2019-08-22 Socket shutdown updates
2019-08-22 Attempting to fix shutdown
2019-08-22 Fixing daemon shutdown
2019-08-23 Catching network errors
2019-08-23 Adding logging on network error
2019-08-24 Adding SSR Value + migration script
2019-08-24 Example updated
2019-08-24 Changing message
2019-08-25 Update example
2019-08-25 changing timeout based on actual network interruption
2019-08-25 Updating ssr period
2019-08-25 fixing syntax error
2019-08-26 Adding seasoning
2019-08-26 Fixing typo
2019-08-26 Allow full on
2019-08-26 Lowering seasoning temp
2019-08-27 Fix for dates after migration
2019-08-28 adjusting schedules based on USDA recommendations
2019-08-29 Updating stages
2019-08-29 Updating note
2019-08-29 Updating header
2019-08-29 Adding new crontab for pigpiod
2019-08-30 Updating tasks
2019-08-30 Adding tri-tip
2019-08-31 Adding ID to board
2019-08-31 Updating add script
2019-08-31 Reorder ID
2019-08-31 Fixing bad error message
2019-09-03 Updated install
2019-09-03 Typo fix
2019-09-04 First steps to PID controller
2019-09-05 cleaning up copied code
2019-09-12 Adding runtime files
2019-09-12 Resolved todos
2019-09-13 Adding PID control
2020-06-01 Shellcheck Updates
2020-06-01 More shellcheck updates

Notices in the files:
kicad/iGrillRPiSSRCtl-revsB/iGrillRPiSSRCtl-rev-sB.kicad_pcb:
License: Creative Commons BY-NC-SA
